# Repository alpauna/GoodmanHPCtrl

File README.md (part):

# GoodmanHPCtrl

ESP32-based controller for Goodman heatpumps with support for cooling, heating, and defrost modes.

> **⚠ Security note:** The device's web interface is plain HTTP only (no built-in TLS). For any access beyond a trusted local LAN, run it behind an HTTPS-terminating reverse proxy (Pangolin, Caddy, nginx, Cloudflare Tunnel, Tailscale Funnel, etc.) — never expose port 80 directly to an untrusted network. See [Network Access](#network-access).

## Web Interface

| Page | Screenshot |
|------|-----------|
| Home |  |
| Dashboard |  |
| Pins |  |
| Configuration |  |
| OTA Update |  |
| Log |  |
| Heap |  |

## Features

- **Relay control** — 4 output pins (FAN, Contactor, W-Heat, Reversing Valve) driven by 4 input signals (Low Pressure Switch, Defrost, Y-Cool, O-Heat)
- **Temperature monitoring** — Up to 6 OneWire (Dallas DS18B20) sensors (compressor, suction, ambient, condenser, liquid, vapor). OneWire sensors discovered on the bus are automatically merged with saved config on boot — new devices get default names and appear immediately without a config reset
- **Subcooling calculation** — Real-time subcooling diagnostic (CONDENSER_TEMP - LIQUID_TEMP) displayed on dashboard when both sensors are valid and compressor is running. Relevant for TXV systems to verify proper refrigerant charge
- **Ambient temp fallback** — 3-tier failover chain for ambient temperature: local OneWire sensor → weather data (MQTT subscription or OpenWeatherMap HTTP API, or both simultaneously) → ESP32 internal die temp. Actively fails up to the best available source every cycle. Configurable staleness timeout, test failover button, dashboard source indicator
- **Remote access** — REST API, WebSocket, MQTT (QoS 1), and CAN bus for monitoring and control
- **Dark/light theme** — Configurable dark/light theme with shared `theme.css` stylesheet. Persisted to SD card config, cached in localStorage for flash-free page loads. Instant preview on config page
- **Admin password protection** — HTTP Basic Auth on sensitive endpoints (`/config`, `/update`, `/ftp`). No password = open access
- **Password encryption** — All passwords (WiFi, MQTT, admin, FTP) encrypted at rest on SD card
- **Live dashboard** — Real-time dashboard at `/dashboard` with state banner, protection status pills with dynamic labels (LPS No Fault/Fault, Temp Ok/Low Temp, Comp Ok/OT, Suct LT Ok/LT, Suct Temp/High Suct with live temp reading, RV Pass/Fail with inline clear button), input/output grid, temperatures, and reboot button. Output indicators include inline status pills:
  -  **SC** (Short Cycle) — Shown on CNT output. Green when inactive, red when CNT short cycle protection delay is active (CNT was off < 5 min, waiting 30s before reactivation)
  -  **DFH** (Defrost Hold) — Shown on CNT, W, and RV outputs during the 3-phase defrost entry and exit transitions. On RV and W: red during entry Phase 1 or exit Phase 1 (pressure equalization). On CNT: red during entry Phase 2 or exit Phase 2 (waiting for CNT short cycle before compressor starts)
- **Pin table with manual override** — Auth-protected `/pins` page showing all GPIO inputs, outputs, and temperatures in a table. "Normal Mode Lockout" checkbox enables manual output control, bypassing the state machine for up to 30 minutes (auto-timeout). CNT enforces short cycle protection even in manual mode. Single auth prompt covers the entire lockout session. "Force Defrost" button triggers a software defrost cycle from HEAT mode (requires no active faults or manual override)
- **Temperature history** — Configurable CSV logging interval (30s-5min, default 2min) per sensor to SD card (`/temps/<sensor>/YYYY-MM-DD.csv`), rolling Canvas line charts on dashboard (6 sensors) with 1h/6h/24h/7d timeframe selector, auto-purge after 31 days
- **Web-based configuration** — HTML pages served from `/www/` on SD card for configuration, OTA updates, and monitoring
- **FTP server** — SimpleFTPServer with timed enable/disable (10/30/60 min) from config page. Configurable password (encrypted on SD card); defaults to `admin`/`admin` when not set. Defaults to OFF; auto-disables after timeout
- **OTA updates** — Firmware upload saves to SD card (`/firmware.new`), then apply to flash. Automatically backs up running firmware with build date metadata before flashing. Supports manual revert and automatic crash recovery (see [Crash Recovery](#crash-recovery))
- **SD card configuration** — WiFi, MQTT, and sensor settings stored as JSON on SD card
- **Multi-output logging** — Serial, MQTT, SD card with tar.gz compressed log rotation, and WebSocket streaming
- **In-memory log buffer** — 500-entry ring buffer in PSRAM, accessible via `/log` API endpoint
- **NTP time sync** — Automatic time synchronization from NTP servers, refreshes every 2 hours
- **I2C bus** — Initialized on GPIO8 (SDA) / GPIO9 (SCL) with automatic device scan at startup and `/i2c/scan` API endpoint
- **PSRAM support** — All heap allocations routed through PSRAM when available
- **WiFi AP fallback** — Configurable timeout (default 10 minutes) before switching to Access Point mode for OTA recovery and reconfiguration
- **CAN bus integration** — Optional CAN bus (ESP32 TWAI, 250 kbps) replaces physical Y/O thermostat wires with CAN messages from AThermostat. Publishes HP state, temperatures, and heartbeat. 10-second timeout safety shuts down compressor if CAN communication is lost. DFT/LPS safety inputs always remain physical. Configurable via `can.enabled` in config JSON. See `docs/canbus-goodmanhp-implementation.md`
- **Multi-unit support** — Configurable system name (max 20 chars, alphanumeric + spaces) and MQTT topic prefix. System name is used as the web UI brand, AP SSID, OLED display name, and auth realm. Multiple controllers can publish to the same MQTT broker with unique prefixes (e.g., `unit1/temps`, `unit2/temps`)
- **FreeRTOS compatible** — Uses `vTaskDelay()` instead of `delay()` for proper RTOS task yielding

## Architecture

### GoodmanHP Controller

The `GoodmanHP` class is the central controller that manages all I/O pins and the heat pump state machine:

- **Pin Management** — Maintains `std::map` collections for input and output pins
  - `addInput(name, pin)` / `addOutput(name, pin)` — Register pins
  - `getInput(name)` / `getOutput(name)` — Access individual pins
  - `getInputMap()` / `getOutputMap()` — Access full pin collections

- **Startup** — All outputs (FAN, CNT, W, RV) are turned OFF on controller startup

- **State Machine** — Tracks heat pump operating mode:
  - `OFF` — No active request
  - `HEAT` — Y input active (heating mode, RV off, W off)
  - `COOL` — Y and O inputs active (cooling mode, RV on, W off)
  - `DEFROST` — DFT emergency defrost or software defrost cycle (W on)
  - `ERROR` — Fault condition active (LPS low pressure); CNT shut down, W follows Y in HEAT mode (Y active, O not active), state updates blocked until fault clears
  - `LOW_TEMP` — Ambient temperature below threshold (default 20°F) for 10 continuous minutes; compressor off, auxiliary heat (W) on, auto-recovers when temp stays above threshold for 10 minutes

- **Output Control by State:**
  - **RV** (reversing valve): ON in COOL, OFF in HEAT/OFF
  - **W** (auxiliary heat): ON in DEFROST, ERROR (HEAT mode only), LOW_TEMP (HEAT mode only), and RV_FAIL (HEAT mode only); OFF otherwise. In COOL mode (Y+O), the system will not operate below 20°F
  - **CNT** (contactor): auto-activates when Y input becomes active, with short cycle protection: if CNT was off for less than 5 minutes, a 30-second delay is enforced before reactivation; if off for 5+ minutes, CNT activates immediately

- **Compressor Over-Temperature Protection** — When COMPRESSOR_TEMP reaches 240°F or above:
  - Immediately shuts down CNT to stop compressor
  - Keeps FAN running to cool the compressor
  - Blocks CNT activation while overtemp is active
  - Rechecks compressor temp every 1 minute
  - Auto-recovers when temp drops below 190°F (50°F hysteresis gap)
  - Logs fault condition and resolution time
  - Highest priority fault — checked before LPS and ambient temp

- **FAN Airflow Safety (Current Watchdog)** — Guarantees the outdoor fan is actually moving air whenever the compressor (CNT) is energized. See [BUG-013](docs/bugs/013-fan-no-current-while-compressor-running.md) for the field failure that motivated this protection:
  - **CNT ⇒ FAN invariant** — every code path that turns CNT ON also asserts FAN ON in the same block (state transitions, HEAT↔COOL cancel path, short-cycle re-activation, `updateState()` output validation) so the outputs cannot desynchronize
  - **Current-based liveness** — `FAN_CURRENT` (SCT-013-030 CT on ADS1115) is polled while CNT is on; if it stays below `FAN_MIN_RUNNING_AMPS` (default 0.3 A) for `FAN_NO_CURRENT_TIMEOUT_MS` (default 20 s), CNT is shut down and the controller latches `ERROR` state for `FAN_FAULT_ERROR_MS` (default 3 min)
  - **Debounced** — requires 3 consecutive low reads before arming the 20 s timer, filtering single-sample I2C glitches from bus contention with WiFi / AsyncTCP / SD log flush
  - **Auto-recovers** after the 3-minute lockout; the watchdog re-arms on the next CNT activation and re-latches if the fan still draws no current
  - Blocks CNT re-activation while the lockout is active; public accessors: `isFanFaultActive()`, `getFanFaultRemainingMs()`, `clearFanFault()`
  - Emits grep-friendly `FAN_FAULT:` and `FAN_SAFETY:` log tags with `Y=`, `O=`, `state=`, `amps=`, `pin=`, `elapsed=` for post-mortem log forensics
  - Depends on `CurrentSensor` producing trustworthy RMS: 60-sample window over ~4 line cycles, DC-mean subtraction, and all-zero I2C reads rejected as invalid rather than published as `0.00 A`

- **Suction Low-Temperature Protection** (COOL mode only) — Monitors SUCTION_TEMP for freezing conditions:
  - Warns when suction temp drops below 34°F
  - Shuts down CNT below 32°F (critically low), keeps FAN running
  - Blocks CNT activation while fault is active
  - Rechecks every 1 minute
  - Auto-recovers when temp rises above 40°F (8°F hysteresis from critical)
  - Auto-clears if mode changes away from COOL
  - Logs fault condition and resolution time

- **LPS Fault Protection** — When the LPS (Low Pressure Switch) input goes LOW:
  - Immediately shuts down CNT if running
  - Sets state to `ERROR`, blocking all state updates
  - Blocks CNT activation while fault is active
  - W (auxiliary heat) continuously follows Y during active fault: ON when Y active and O not active (HEAT mode), OFF when Y drops or O active (COOL mode). W is never turned on in COOL mode
  - Auto-recovers when LPS goes HIGH; W turned off, short-cycle protection (30s delay) is enforced on CNT reactivation
  - Publishes fault events via MQTT (`goodman/fault` topic)

- **Low Ambient Temperature Protection** — When AMBIENT_TEMP drops below the configurable threshold (default 20°F):
  - **10-minute validation delay** in both directions: temp must stay below threshold for 10 continuous minutes before entering LOW_TEMP, and above threshold for 10 continuous minutes before exiting. If temp reverses during the validation window, the pending transition is cancelled. Prevents fluttering near the threshold
  - Enters `LOW_TEMP` state: shuts down CNT, turns off FAN and RV
  - Turns on W (auxiliary heat) in HEAT mode only
  - If thermostat switches to COOL mode (Y+O) while in LOW_TEMP, W is turned off — no heating or cooling operates below 20°F in COOL mode
  - Blocks all compressor activation (CNT) while ambient temp is too low
  - Auto-recovers when temperature stays above threshold for 10 minutes
  - Threshold is configurable via `lowTemp.threshold` in SD card config

- **Ambient Temperature Fallback (3-Tier)** — When the local AMBIENT_TEMP OneWire sensor is unavailable, the system falls through a priority chain to maintain ambient awareness:
  1. **Local sensor** (primary) — OneWire DS18B20, highest accuracy
  2. **Weather data** (failover) — Cached outdoor temperature from a configurable source:
     - **MQTT**: Subscribes (QoS 1) to a configurable topic (e.g., `homeassistant/sensor/outdoor_temp/state`) and parses plain float payloads
     - **HTTP**: Polls OpenWeatherMap API at a configurable interval (default 10 min, range 1–60)
     - **MQTT + HTTP**: Both run simultaneously — MQTT delivers faster push updates while HTTP acts as a safety net if MQTT stops publishing. Most recent update from either source wins
  3. **ESP32 internal temp** (last resort) — Die temperature via `temperatureRead()`, converted C→F. Reads higher than true ambient but catches genuinely cold conditions
  - **Fail-up**: The fallback chain re-evaluates every 10s cycle and actively promotes to the best available source — INTERNAL→WEATHER when weather data arrives, any fallback→SENSOR when the real sensor recovers
  - Weather data is cached with a configurable staleness timeout (default 30 minutes). Stale weather with no local sensor falls through to ESP32 internal temp
  - `ambientSource` field in `/state` JSON and MQTT state tracks the active source: `"sensor"`, `"weather"`, or `"internal"`
  - Dashboard shows a source-aware ambient pill (green for sensor, orange for weather/internal) and a "Weather Amb (failover)" row with the cached temperature and age
  - Output state validator enforces CNT OFF when no ambient data is available (sensor invalid + no weather)
  - Config page "Weather Ambient Fallback" fieldset: source dropdown (None/MQTT/HTTP/MQTT + HTTP), conditional MQTT topic or HTTP API key/ZIP/country fields, staleness timeout
  - **Test Failover** button on config page forces the ambient sensor offline for 30 minutes to verify the fallback chain
  - Configured via `weather` section in SD card config JSON. API key encrypted with same `$AES$`/`$ENC$` scheme as other passwords

- **Input Pin Validation Delay** — All 4 input pins (LPS, DFT, Y, O) use a configurable debounce/validation delay (default 2 seconds) to prevent false triggers from electrical noise or transient signals:
  - Input pins are polled every 500ms via `onCheckInputQueue()` (direct GPIO polling, no ISR attachment required)
  - When a pin's live GPIO state differs from its confirmed state, a validation timer starts
  - After the delay expires, the GPIO is re-read to confirm the pin is still in the expected state
  - If the pin has reverted to its original state, the change is discarded as a false trigger and logged as a warning
  - `isActive()` returns the confirmed/debounced state, not the live GPIO — the state machine only sees validated inputs
  - `getPendingState()` prevents re-triggering while a validation is already in progress
  - Both activation (pin going HIGH) and deactivation (pin going LOW) go through the full delay
  - Configurable via `heatpump.inputDelay.ms` in config JSON (0–60 seconds, live — changes apply immediately to all input pins)

- **State Validation Delay** — After any state transition (e.g., OFF→HEAT, HEAT→COOL), the system holds the new state for a configurable period (default 30 seconds) before allowing another normal-priority state change. This prevents rapid state cycling:
  - **HIGH priority** states (OFF, ERROR) bypass the validation timer entirely
  - **NORMAL priority** states (HEAT, COOL, DEFROST, LOW_TEMP) are gated — blocked until the timer expires
  - LOW_TEMP has special handling: output protection (CNT/FAN/RV off, W management) is applied immediately, but the state label is deferred until validation completes
  - Dashboard shows a "State Hold" pill (blue) with countdown during validation
  - Configurable via `heatpump.stateValidation.delayMs` in config JSON (0–300 seconds, live)

- **Output State Validation** — Every 10 seconds, `validateOutputStates()` verifies all relay outputs match the expected state for the current operating mode using a table-driven approach:
  - **Global invariants** enforced first: W must never be on when O is active; CNT must be off during any blocking fault (priority: compressor overtemp > suction low temp > LPS fault > low temp > RV fail)
  - **Per-state table** defines expected output values: OFF=all off, COOL=RV on/W off, HEAT=RV off, DEFROST Ph3=RV+W on/FAN off, ERROR=CNT off, LOW_TEMP=CNT+FAN+RV off
  - **Transition phase rows** validated: COOL Trans Ph1/Ph2, HEAT Trans Ph1/Ph2, DEFROST Ph1/Ph2, Defrost Exit Ph1/Ph2
  - Mismatches are logged as errors and auto-corrected
  - Skipped during startup lockout and manual override only (transitions are now validated)
  - Manual override also bypasses the state validation timer so it doesn't interfere with manual pin control testing
  - Logs "State check OK" at info level every 30 seconds when all outputs are correct

- **Adaptive Defrost Bands** — Colder ambient temperatures cause faster ice buildup on the outdoor coil, requiring more frequent defrost cycles. Instead of a single fixed runtime threshold, the controller uses 3 ambient temperature bands — each with its own heat runtime threshold, minimum defrost duration, and condenser exit temperature:

  | Band | Ambient Range | Runtime Threshold | Min Defrost | Condenser Exit Temp |
  |------|--------------|-------------------|-------------|---------------------|
  | **Cold** | ≤ 23°F | 30 min | 2 min | 50°F |
  | **Mid** | 23–31°F | 60 min | 1.5 min | 55°F |
  | **Warm** | ≥ 31°F | 90 min | 1 min | 60°F |

  All values are configurable via the config page "Defrost Bands" fieldset. The two breakpoint temperatures (`coldMaxTemp`, `warmMinTemp`) define the band boundaries and can be adjusted independently.

  **How it works:**
  - The active band is selected every update cycle based on the current ambient temperature (using the same 3-tier fallback: sensor → weather → ESP32 internal temp)
  - When no ambient data is available, the system defaults to the **Warm** band (most conservative — longest runtime before defrost triggers)
  - When defrost starts, the active band's parameters are **snapshotted** and frozen for the duration of the cycle. If ambient temperature drifts mid-defrost (e.g., the sun comes up), the exit criteria stay stable — no mid-cycle parameter jumps
  - Dashboard and OLED display show the current band and progress: `Heat RT: 42m / 60m (Mid)`
  - `/state` JSON includes `defrostBand` (active band name) and `defrostBandThresholdMin` (active threshold in minutes)

  **Config JSON structure:**
  ```json
  "defrost": {
      "active": false,
      "coldMaxTemp": 23.0,
      "warmMinTemp": 31.0,
      "cold": { "runtimeThresholdMs": 1800000, "minRuntimeMs": 120000, "exitTempF": 50.0 },
      "mid":  { "runtimeThresholdMs": 3600000, "minRuntimeMs": 90000,  "exitTempF": 55.0 },
      "warm": { "runtimeThresholdMs": 5400000, "minRuntimeMs": 60000,  "exitTempF": 60.0 }
  }
  ```

  **Backward compatibility:** Devices upgrading from firmware with single-value defrost settings (`heatRuntimeThresholdMs`, `minRuntimeMs`, `exitTempF`) auto-migrate on first config load. The old values become the Warm band, and Mid/Cold bands are derived proportionally. Old keys are removed on the next config save.

- **Automatic Defrost (3-Phase Sequencing)** — After the active band's heat runtime threshold of accumulated CNT runtime in HEAT mode while DFT is active (coil temp ≤ 32°F, indicating icing conditions), initiates a 3-phase software defrost cycle for safe pressure equalization and output sequencing:

  **Phase 1 — Pressure Equalization** (`defrostTransition`):
  - All outputs OFF (CNT, FAN, W, RV)
  - Duration: `heatpump.shortCycle.rv` (default 30s)
  - Allows system pressures to equalize before reversing valve switches

  **Phase 2 — RV + W Engaged, CNT Hold** (`defrostCntPending`):
  - RV and W turned ON, CNT remains OFF
  - Duration: `heatpump.shortCycle.cnt` (default 30s)
  - Allows reversing valve to fully seat before compressor starts

  **Phase 3 — Active Defrost**:
  - CNT turned ON, defrost fully active
  - Runs for at least the active band's minimum defrost time before checking exit conditions
  - Rechecks CONDENSER_TEMP every 1 minute during defrost with logging
  - Exits when CONDENSER_TEMP >= the active band's exit temperature or 15-minute safety timeout

- **Defrost Exit Transition (3-Phase)** — When defrost completes (condenser temp reached or timeout), the system performs a reverse 3-phase sequence to safely switch the reversing valve back to heat position before restarting the compressor:

  **Exit Phase 1 — Pressure Equalization** (`defrostTransition` + `defrostExiting`):
  - CNT, FAN, and W turned OFF immediately; RV stays ON
  - Duration: `heatpump.shortCycle.rv` (default 30s)
  - Allows system pressures to equalize after compressor stops

  **Exit Phase 2 — RV Switch + CNT Hold** (`defrostCntPending` + `defrostExiting`):
  - RV turned OFF (switches back to heat position), CNT remains OFF
  - Duration: `heatpump.shortCycle.cnt` (default 30s)
  - Allows reversing valve to physically seat before compressor restarts

  **Exit Complete**:
  - CNT and FAN turned ON — system resumes normal HEAT mode operation
  - State machine has already transitioned from DEFROST to HEAT at exit start

  **Additional defrost behavior:**
  - Heat runtime only accumulates when DFT input is active (closed at 32°F, indicating icing conditions)
  - DFT turning off (temps > 32°F) clears accumulated runtime after a 30-second debounce — prevents false resets from intermittent DFT wire contact
  - Only COOL and DEFROST modes clear accumulated runtime; Y going off does not
  - Only HEAT mode adds time to accumulated runtime
  - Runtime persists to SD card every 5 minutes, restored on boot
  - **Y drop during defrost entry**: All outputs turn off (including W), transition flags are cleared, but `_softwareDefrost` stays set. When Y reactivates in HEAT mode, defrost restarts from Phase 1
  - **Y drop during defrost exit**: All outputs turn off, exit transition cancelled. Normal state machine resumes on Y reactivation
  - **COOL cancellation**: If the thermostat switches to COOL mode (O becomes active) during any phase of a pending defrost, the defrost is cancelled entirely, heat runtime is cleared, and the system enters normal COOL mode

- **HEAT→COOL Mode Transition (3-Phase)** — When switching from HEAT to COOL (O input activates), the reversing valve must switch safely with the compressor stopped:

  **Phase 1 — Pressure Equalization** (`coolTransition`):
  - CNT and FAN turned OFF, RV stays OFF (from HEAT position)
  - Duration: `heatpump.shortCycle.rv` (default 30s)

  **Phase 2 — RV On + CNT Hold** (`coolCntPending`):
  - RV turned ON (switches to COOL position), CNT remains OFF
  - Duration: `heatpump.shortCycle.cnt` (default 30s)

  **Complete**: CNT and FAN turned ON — normal COOL mode active. If RV is already ON (e.g., from defrost Phase 2/3→COOL), the transition is skipped.

- **COOL→HEAT Mode Transition (3-Phase)** — When switching from COOL to HEAT (O input deactivates), the reversing valve must switch safely with the compressor stopped:

  **Phase 1 — Pressure Equalization** (`heatTransition`):
  - CNT and FAN turned OFF, RV stays ON (from COOL position)
  - Duration: `heatpump.shortCycle.rv` (default 30s)

  **Phase 2 — RV Off + CNT Hold** (`heatCntPending`):
  - RV turned OFF (switches to HEAT position), CNT remains OFF
  - Duration: `heatpump.shortCycle.cnt` (default 30s)

  **Complete**: CNT and FAN turned ON — normal HEAT mode active.

  Both mode transitions abort on Y drop or state change (fault/LOW_TEMP), turning all outputs off.

### State Table

| State | Condition | FAN | CNT | RV | W | Notes |
|-------|-----------|-----|-----|----|---|-------|
| `OFF` | Y inactive | OFF | OFF | OFF | OFF | All outputs off |
| `HEAT` | Y active, O inactive | ON | ON | OFF | OFF | CNT has 30s short-cycle protection |
| `COOL` | Y active, O active | ON | ON | ON | OFF | Will not operate below 20°F |
| `DEFROST` Phase 1 | Pressure equalization (30s) | OFF | OFF | OFF | OFF | All outputs off for pressure equalization |
| `DEFROST` Phase 2 | RV + W engaged, CNT hold (30s) | OFF | OFF | ON | ON | Reversing valve seats before compressor starts |
| `DEFROST` Phase 3 | Active defrost | OFF | ON | ON | ON | Band-specific min time/exit temp (see Adaptive Defrost Bands), 15-min safety timeout |
| `HEAT` Exit Phase 1 | Defrost exit pressure equalization (30s) | OFF | OFF | ON | ON | RV+W stay on from defrost, CNT+FAN off |
| `HEAT` Exit Phase 2 | RV switch + CNT hold (30s) | OFF | OFF | OFF | OFF | RV switches back to heat position |
| `HEAT` Exit Complete | CNT+FAN resume | ON | ON | OFF | OFF | Normal HEAT mode resumes |
| `COOL` Trans Phase 1 | HEAT→COOL pressure equalization (30s) | OFF | OFF | OFF | OFF | CNT+FAN off before RV switches |
| `COOL` Trans Phase 2 | RV on, CNT hold (30s) | OFF | OFF | ON | OFF | RV seats before compressor starts |
| `HEAT` Trans Phase 1 | COOL→HEAT pressure equalization (30s) | OFF | OFF | ON | OFF | CNT+FAN off, RV still on from COOL |
| `HEAT` Trans Phase 2 | RV off, CNT hold (30s) | OFF | OFF | OFF | OFF | RV switches to HEAT position |
| `ERROR` | LPS fault (low pressure) | OFF | OFF | OFF | ON* | *W on only in HEAT mode (Y active, O inactive) |
| `LOW_TEMP` | Ambient < 20°F | OFF | OFF | OFF | ON* | *W on only in HEAT mode; W turns off if thermostat switches to COOL (Y+O) |
| `HEAT` + RV Fail | RV fail latched | ON | OFF | OFF | ON* | *W on only in HEAT mode; CNT blocked until cleared |

**Fault Conditions** (overlay on current state, block CNT activation):

| Fault | Condition | Trigger | Recovery | FAN | CNT | W | Priority |
|-------|-----------|---------|----------|-----|-----|---|----------|
| Compressor overtemp | COMPRESSOR_TEMP ≥ 240°F | Any mode | Temp < 190°F | ON | OFF | OFF | 1 (highest) |
| Suction low temp | SUCTION_TEMP < 32°F | COOL mode only | Temp > 40°F | ON | OFF | OFF | 2 |
| LPS fault | LPS input LOW | Any mode | LPS goes HIGH | OFF | OFF | ON* | 3 |
| Low ambient temp | AMBIENT_TEMP < 20°F for 10 min | Any mode | Temp ≥ 20°F for 10 min | OFF | OFF | ON* | 4 |
| RV fail | SUCTION_TEMP ≥ 140°F during defrost | Defrost only | Manual clear via dashboard/config | ON | OFF | ON* | Latched |

\* W on only in HEAT mode (Y active, O inactive); never activated in COOL mode (Y+O).

**Fault Priority:** Compressor overtemp > Suction low temp > LPS fault > Low ambient temp. Higher-priority faults take precedence; lower-priority checks are skipped while a higher-priority fault is active.

### Class Structure

| Class | Purpose |
|-------|---------|
| `GoodmanHP` | Central controller with pin maps, temp sensors, and state machine |
| `InputPin` | Digital/analog input with polling-based validation delay, confirmed-state debouncing, callbacks |
| `OutPin` | Output relay with delay, PWM support, state tracking, hardware state validation |
| `TempSensor` | OneWire (DS18B20) temperature sensor with callbacks. 6 default names: COMPRESSOR, SUCTION, AMBIENT, CONDENSER, LIQUID, VAPOR |
| `Config` | SD card and JSON configuration management |
| `Logger` | Multi-output logging with tar.gz rotation, ring buffer, and WebSocket streaming |
| `WebHandler` | AsyncWebServer (port 80) with REST API and WebSocket |
| `MQTTHandler` | MQTT client with auto-reconnect and topic publishing |

## Hardware

**Supported boards:**
- Freenove ESP32-S3-WROOM (primary)
- ESP32 DevKit

**GPIO Pin Mapping (ESP32-S3):**

| Pin | GPIO | Direction | Description |
|-----|------|-----------|-------------|
| LPS | 15 | Input | Low Pressure Switch |
| DFT | 16 | Input | Defrost signal |
| Y | 17 | Input | Compressor request (heat or cool) |
| O | 18 | Input | Reversing valve signal (cool mode) |
| FAN | 4 | Output | Fan relay |
| CNT | 5 | Output | Contactor relay (3s delay) |
| W | 6 | Output | Heating relay |
| RV | 7 | Output | Reversing valve relay |
| SDA | 8 | I/O | I2C data |
| SCL | 9 | I/O | I2C clock |
| OneWire | 21 | I/O | Temperature sensor bus |
| CAN TX | 38 | Output | CAN bus transmit (TWAI) |
| CAN RX | 14 | Input | CAN bus receive (TWAI) |

**I2C Devices:**

| Device | Address | Description |
|--------|---------|-------------|
| SSD1306 | 0x3C | 128x64 OLED display (5-page auto-cycling status) |
| ADS1115 | 0x48 | 16-bit ADC for CT clamp current sensing |

### 3D Printed Shell

The enclosure is an EasyEDA-exported 3D shell, post-processed with FreeCAD Python scripts for thicker walls, a flipped mating profile, and mounting hardware. All files are in the `shell/` directory.

**Shell files:**

| File | Description |
|------|-------------|
| `3DShell_GoodmanHPv3_T_3mm_TC.step/.stl` | Original top shell (3mm walls, tongue on outer half, TC mount) |
| `3DShell_GoodmanHPv3_B_3mm.step/.stl` | Original bottom shell (3mm walls, groove on outer half) |
| `3DShell_GoodmanHPv3_T_3.5mm_TC_flipped.step/.stl` | Modified top shell (3.5mm walls, groove replaces tongue) |
| `3DShell_GoodmanHPv3_B_3.5mm_flipped.step/.stl` | Modified bottom shell (3.5mm walls, tongue replaces groove) |
| `modify_top.py` | FreeCAD script to generate the modified top shell |
| `modify_bottom.py` | FreeCAD script to generate the modified bottom shell |
| `cutout.py` | Reusable FreeCAD utility library for cutout, standoff, and mounting operations |

**Why the mating profile was flipped:** The original design had a tongue (raised band) on the top shell mating rim. When 3D printed, this thin horizontal band is prone to layer separation because it prints as an unsupported overhang at the shell's open edge. Moving the tongue to the bottom shell and the groove to the top eliminates this — the bottom tongue prints vertically up from the floor (strong layer adhesion), and the top groove is simply a recess in a solid wall.

**Modifications applied:**

1. **Wall thickening (3mm to 3.5mm)** — 0.5mm added to the outer face of all 4 walls. Inner cavity dimensions unchanged so the PCB still fits. Wall cutouts (connector openings on right and back walls) are preserved by pre-cutting matching holes in the thickening ring before fusing.

2. **Mating profile flip** — The rabbet/step joint between shells was inverted:
   - **Bottom**: Original groove (Z=31-35) filled, new outer tongue added with 0.10mm clearance per side
   - **Top**: Original tongue (Z=28-32) removed, new inner lip + outer groove cut

3. **M3 screw pillar** — 5mm OD, 3mm tall pillar on the top shell ceiling for mounting the MAX6675 thermocouple board, with M3 (2.5mm) through-hole centered in the pillar

**Utility library (`cutout.py`):**

Composable functions for shell modifications. Each takes a `Part.Shape` and returns a modified shape. OCCT boolean operation quirks (oversized plugs, Z range matching, flush trimming) are handled internally:

| Function | Purpose |
|----------|---------|
| `rectangular_cutout()` | Cut a window through a Z-normal surface |
| `reposition_cutout()` | Plug an existing cutout and re-cut at a new position (3-step: oversized plug, matching-Z cut, flush trim) |
| `add_standoff()` | Fuse a cylindrical pillar onto a surface (with auto-trim for reliable OCCT fuse) |
| `drill_hole()` | Vertical through-hole along Z axis |
| `drill_hole_lateral()` | Horizontal through-hole along X or Y axis (screw holes through walls) |
| `add_standoffs_with_holes()` | Multiple standoffs + centered screw holes (convenience combo) |
| `wall_ring()` | Rectangular ring (outer box minus inner box) for wall thickening and mating profiles |
| `z_probe()` | Probe Z intersections at an XY point (verification) |
| `verify_cutout()` | Check a rectangular cutout is fully open (probes center + corners) |
| `verify_solid()` | Check material exists at a point between two Z levels |

Example usage:
```python
from cutout import reposition_cutout, add_standoff, drill_hole

# Reposition an LCD cutout (plug old hole, cut new, trim flush — all in one call)
result = reposition_cutout(result,
    old_x1=-38.48, old_y1=59.59, old_x2=-11.43, old_y2=76.59,
    new_x1=-38.48, new_y1=61.59, new_x2=-11.43, new_y2=77.59,
    z_inner=48.50, z_outer=51.50)

# Add a mounting standoff below the ceiling
result = add_standoff(result, cx=-63.76, cy=67.14,
    z_surface=48.50, height=3.0, radius=2.5, z_outer=51.50)

# Drill a screw hole through the standoff
result = drill_hole(result, cx=-63.76, cy=67.14,
    z_bottom=45.50, z_top=51.50, radius=1.25)
```

**Regenerating modified shells:**

```bash
# Requires FreeCAD installed (sudo apt install freecad)
freecadcmd shell/modify_top.py
freecadcmd shell/modify_bottom.py
```

**Key geometry constants (all in mm, origin at EasyEDA export origin):**

| Constant | Value | Description |
|----------|-------|-------------|
| Outer walls | X[-98.26, 4.92] Y[-32.48, 97.12] | Original 3mm outer face |
| Inner walls | X[-95.26, 1.92] Y[-29.48, 94.12] | Original 3mm inner face |
| New outer | X[-98.76, 5.42] Y[-32.98, 97.62] | After 0.5mm thickening |
| Bottom mating zone | Z=31 to Z=35 | Groove (original) / Tongue (modified) |
| Top mating zone | Z=28 to Z=32 | Tongue (original) / Groove (modified) |
| Right wall cutout | Y[47, 88.5] Z[7, 24] | Connector opening, +X wall |
| Back wall lower cutout | X[-50, -35] Z[6, 13] | Opening, +Y wall |
| Back wall upper cutout | X[-89.5, -3.5] Z[14, 17] | Opening, +Y wall |

### Modifying EasyEDA 3D Shell Exports with Claude Code

EasyEDA exports PCB enclosures as STEP files with thin walls (typically 1.5mm). These often need post-processing — thicker walls, mating features, mounting hardware, cutouts — which can be done programmatically via FreeCAD's Python API and Claude Code. Below is a reusable prompt template and the key lessons learned from this project's shell modifications.

**Prerequisites:** `freecad` package installed (`sudo apt install freecad`), STEP files exported from EasyEDA's 3D shell generator.

**Prompt template** — adapt the bracketed sections to your project:

> I have EasyEDA-exported STEP enclosure shells at `[path/to/shells/]`:
> - `[Bottom_Shell.step]` — bottom half, open top
> - `[Top_Shell.step]` — top half, open bottom
>
> The shells have [1.5mm] walls. I need the following modifications:
>
> 1. **Wall thickening** — Increase wall thickness from [1.5mm] to [3mm] by expanding outward. Keep inner cavity dimensions identical to the original so the PCB still fits. Preserve all interior features (screw pillars, standoffs, alignment posts) from the original STEP by extracting them via boolean intersection and fusing them back into the thickened shell.
>
> 2. **Mating joint** — Add a rabbet/step joint between top and bottom shells in the overlap zone where both rims meet:
>    - Bottom: remove outer half of wall for [4mm] from the rim (groove)
>    - Top: remove inner half of wall in the overlap zone + add outer-half tongue extending [4mm] below the rim with [0.2mm] clearance
>    - The tongue must overlap at least [2mm] into existing wall geometry above the rim for OCCT fuse to succeed (coincident-face workaround)
>
> 3. **Screw holes** — Drill [M1.2] through-holes at [left and right wall midpoints], centered in the interlocking overlap zone so the screw passes through both the tongue and groove lip
>
> 4. **Cutouts** — Cut rectangular openings in the top shell for: [LCD window at X1,Y1 to X2,Y2], [wire pass-through at ...], [connector at ...]
>
> 5. **Mounting features** — Add a screw pillar on the inner ceiling of the top shell at [position] for mounting a [component]. [Xmm] OD, [Xmm] tall, [MX] tap hole
>
> Write a FreeCAD Python script (`freecadcmd script.py`) that loads the STEP files, performs all modifications via boolean operations, and exports both STL and STEP. Include a verification section that cross-sections the results and prints geometry at key Z levels.

**Key lessons for FreeCAD/OCCT boolean operations:**

| Issue | Symptom | Fix |
|-------|---------|-----|
| Coincident face fuse failure | `fuse()` adds volume but geometry doesn't extend beyond shared face | Extend the new body 1-2mm past the shared face into existing solid so they overlap, not just touch |
| `makeOffsetShape` fails on complex shells | Exception or degenerate result | Rebuild parametrically: create outer box, cut inner cavity, extract+fuse interior features from original via `common()` |
| Thickening shifts features | Mounting tabs, screw pillars stay at original positions | After thickening, extract features by region (`common()` with probe box), `translated()` to correct position, cut old + fuse shifted |
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
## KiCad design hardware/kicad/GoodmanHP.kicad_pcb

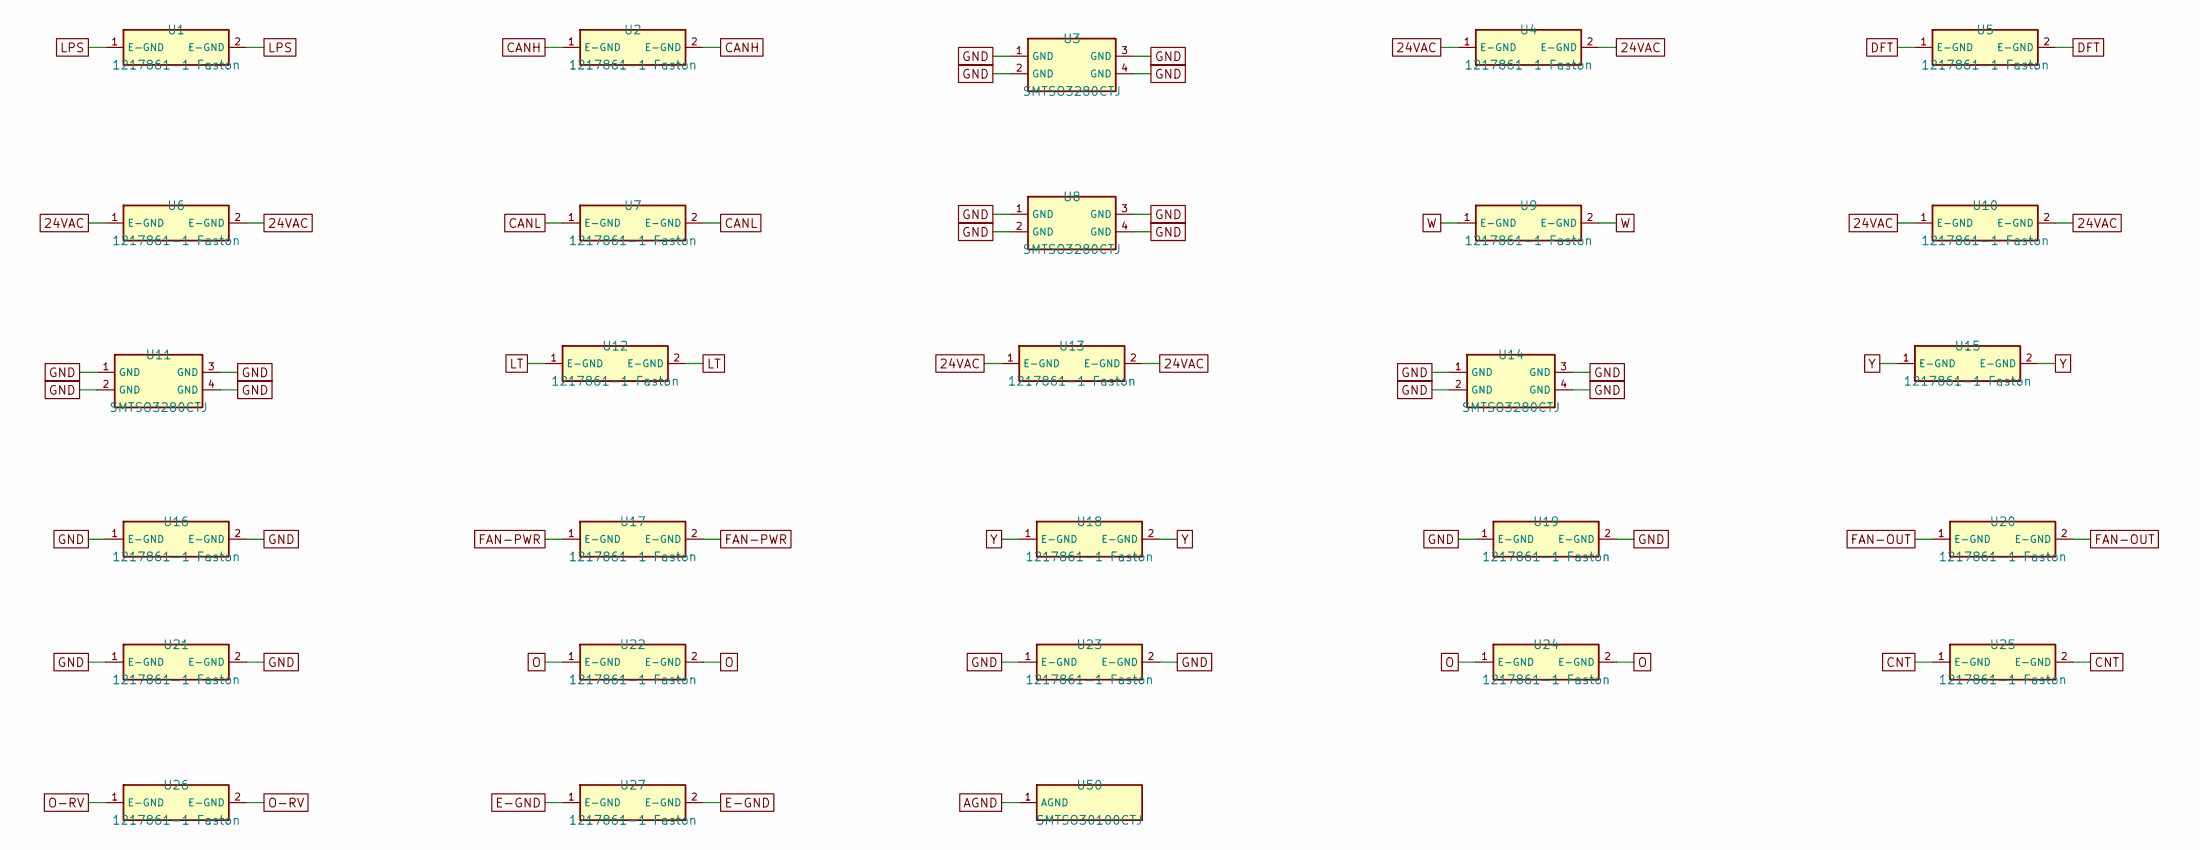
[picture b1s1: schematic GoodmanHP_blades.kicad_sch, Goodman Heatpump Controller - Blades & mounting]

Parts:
U1, U2, U4, U5, U6, U7, U9, U10, U12, U13, U15, U16, U17, U18, U19, U20, U21, U22, U23, U24, U25, U26, U27: 1217861-1 Faston; 1217861-1; LCSC C428480
U3, U8, U11, U14: SMTSO3280CTJ; SMD_BD5.6-L5.6-W5.6-D4.1; LCSC C2928174
U50: SMTSO30100CTJ; SCREW-SMD_BD5.6-D4.1-H10; LCSC C2916370

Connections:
24VAC: U4.1, U4.2, U6.1, U6.2, U10.1, U10.2, U13.1, U13.2; also elsewhere on the board
AGND: U50.1; also elsewhere on the board
CANH: U2.1, U2.2; also elsewhere on the board
CANL: U7.1, U7.2; also elsewhere on the board
CNT: U25.1, U25.2; also elsewhere on the board
DFT: U5.1, U5.2; also elsewhere on the board
E-GND: U27.1, U27.2; also elsewhere on the board
FAN-OUT: U20.1, U20.2; also elsewhere on the board
FAN-PWR: U17.1, U17.2; also elsewhere on the board
GND: U3.1, U3.2, U3.3, U3.4, U8.1, U8.2, U8.3, U8.4, U11.1, U11.2, U11.3, U11.4, U14.1, U14.2, U14.3, U14.4, U16.1, U16.2, U19.1, U19.2, U21.1, U21.2, U23.1, U23.2; also elsewhere on the board
LPS: U1.1, U1.2; also elsewhere on the board
LT: U12.1, U12.2; also elsewhere on the board
O: U22.1, U22.2, U24.1, U24.2; also elsewhere on the board
O-RV: U26.1, U26.2; also elsewhere on the board
W: U9.1, U9.2; also elsewhere on the board
Y: U15.1, U15.2, U18.1, U18.2; also elsewhere on the board

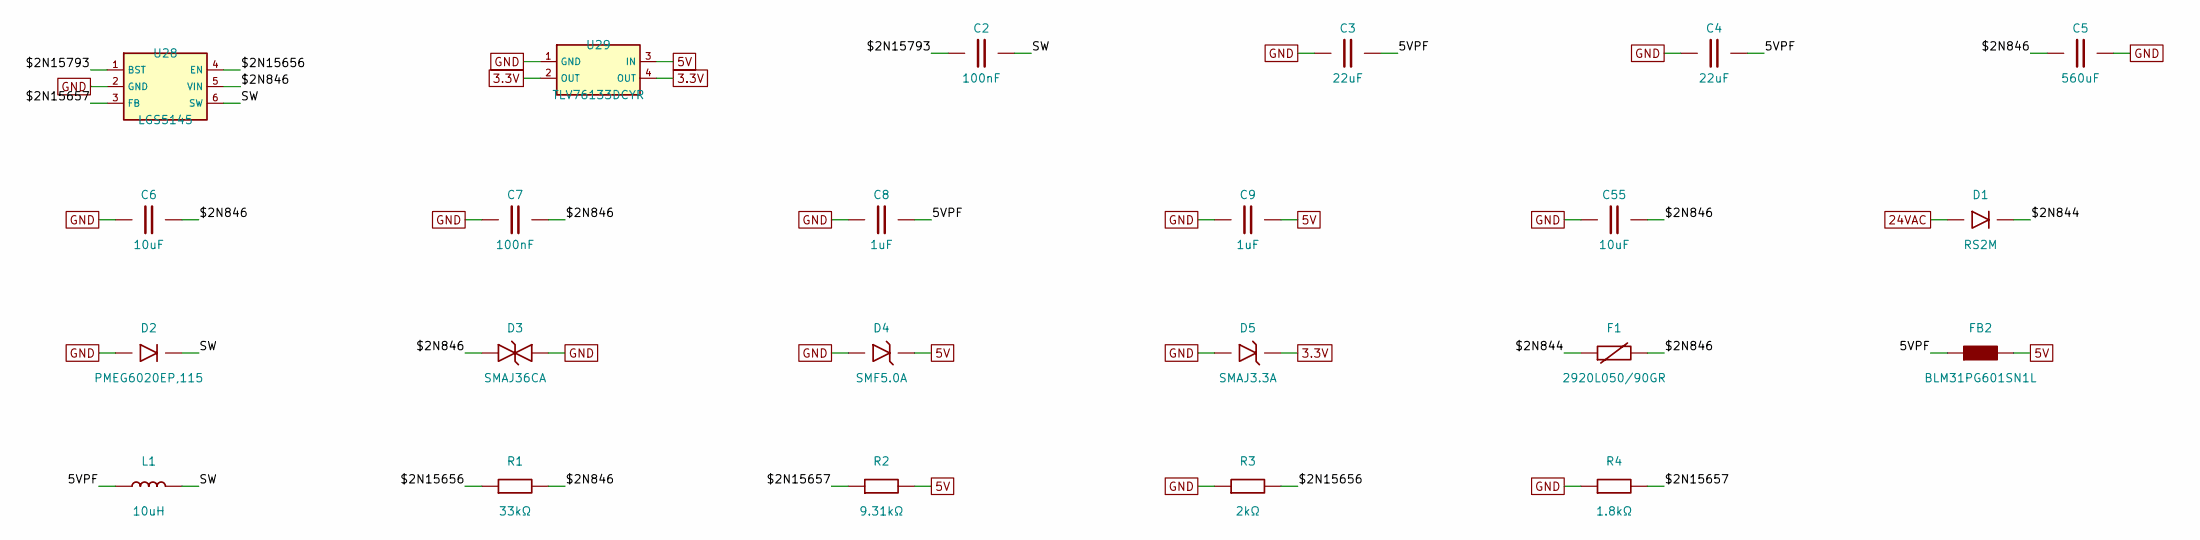
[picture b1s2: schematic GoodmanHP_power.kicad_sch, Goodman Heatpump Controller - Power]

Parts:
C2, C7: 100nF; C0402; LCSC C77020
C3, C4: 22uF; C0805; LCSC C907991
C5: 560uF; CAP-TH_BD10.0-P5.00-D1.0-FD_1; LCSC C49309240
C6, C55: 10uF; C1210; LCSC C437568
C8, C9: 1uF; C0201; LCSC C76929
D1: RS2M; SMA_L4.3-W2.7-LS5.1-RD; LCSC C908426
D2: PMEG6020EP,115; SOD-128_L3.7-W2.5-LS4.7-FD; LCSC C179433
D3: SMAJ36CA; SMA_L4.2-W2.7-LS5.0-BI; LCSC C908830
D4: SMF5.0A; SOD-123FL_L2.8-W1.9-LS3.7-RD; LCSC C2857263
D5: SMAJ3.3A; SMA_L4.3-W2.7-LS5.1-RD; LCSC C22365220
F1: 2920L050/90GR; F2920; LCSC C41414044
FB2: BLM31PG601SN1L; L1206; LCSC C16902
L1: 10uH; IND-SMD_L2.5-W2.0; LCSC C5832376
R1: 33kΩ; R0201; LCSC C473534
R2: 9.31kΩ; R0201; LCSC C423401
R3: 2kΩ; R0201; LCSC C851709
R4: 1.8kΩ; R0201; LCSC C473568
U28: LGS5145; SOT-23-6_L2.9-W1.7-P0.95-LS2.8-BL; LCSC C5123971
U29: TLV76133DCYR; SOT-223-4_L6.5-W3.5-P2.30-LS7.0-TR; LCSC C7527500

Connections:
3.3V: D5.1 (K), U29.2 (OUT), U29.4 (OUT); also elsewhere on the board
5V: C9.2, D4.1 (K), FB2.2, R2.2, U29.3 (IN); also elsewhere on the board
5VPF: C3.2, C4.2, C8.2, FB2.1, L1.1
24VAC: D1.2 (A); also elsewhere on the board
$2N844: D1.1 (K), F1.1
$2N846: C5.1, C6.2, C7.2, C55.2, D3.1, F1.2, R1.2, U28.5 (VIN)
$2N15656: R1.1, R3.2, U28.4 (EN)
$2N15657: R2.1, R4.2, U28.3 (FB)
$2N15793: C2.1, U28.1 (BST)
GND: C3.1, C4.1, C5.2, C6.1, C7.1, C8.1, C9.1, C55.1, D2.2 (A), D3.2, D4.2 (A), D5.2 (A), R3.1, R4.1, U28.2 (GND), U29.1 (GND); also elsewhere on the board
SW: C2.2, D2.1 (K), L1.2, U28.6 (SW)

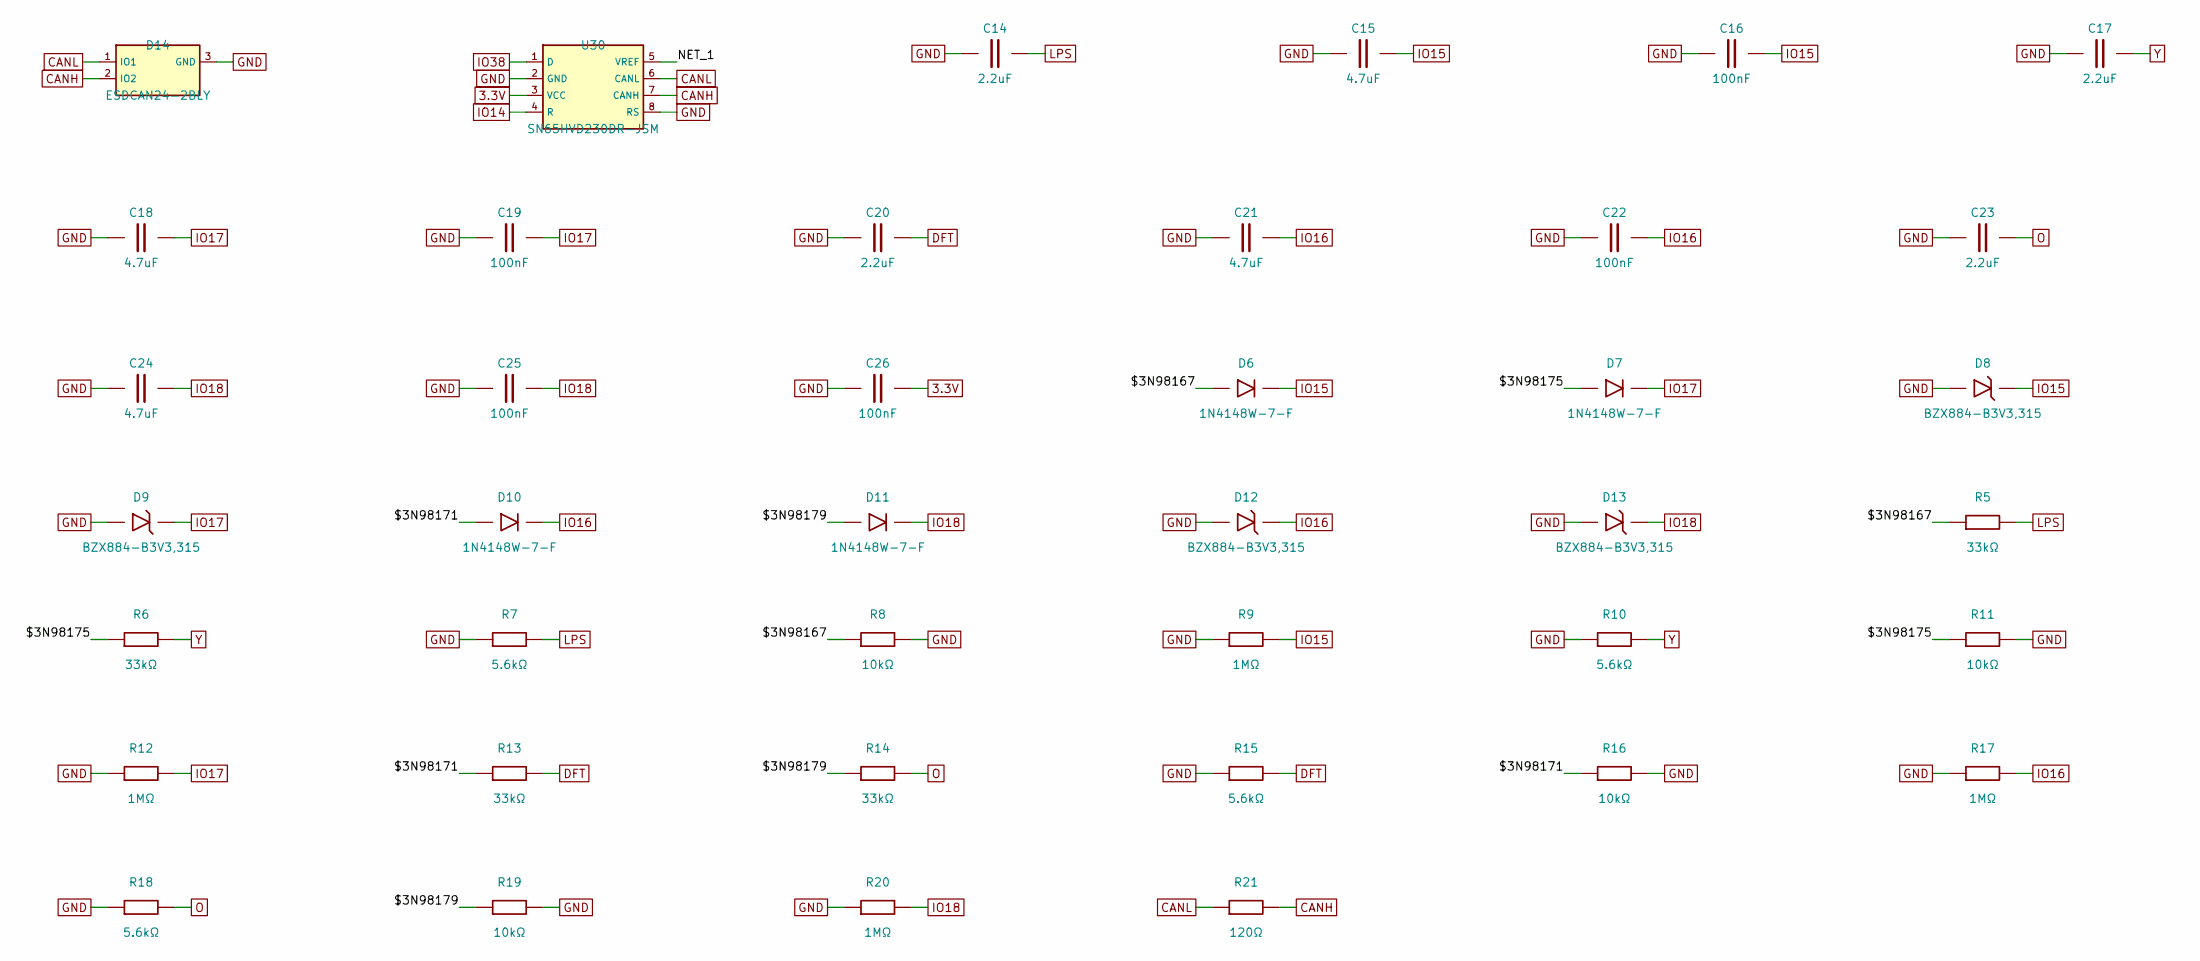
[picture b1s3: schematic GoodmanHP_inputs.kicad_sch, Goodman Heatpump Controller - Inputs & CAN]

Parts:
C14, C17, C20, C23: 2.2uF; C0805; LCSC C22367838
C15, C18, C21, C24: 4.7uF; C0402; LCSC C20624278
C16, C19, C22, C25, C26: 100nF; C0201; LCSC C85923
D6, D7, D10, D11: 1N4148W-7-F; SOD-123_L2.7-W1.6-LS3.7-RD-1; LCSC C83528
D8, D9, D12, D13: BZX884-B3V3,315; SOD-882_L1.0-W0.6-RD; LCSC C551199
D14: ESDCAN24-2BLY; SOT-23-3_L2.9-W1.3-P1.90-LS2.4-BL-2; LCSC C2937021
R5, R6, R13, R14: 33kΩ; R0201; LCSC C473534
R7, R10, R15, R18: 5.6kΩ; R0805; LCSC C441985
R8, R11, R16, R19: 10kΩ; R0201; LCSC C473048
R9, R12, R17, R20: 1MΩ; R0201; LCSC C295786
R21: 120Ω; R0805; LCSC C844392
U30: SN65HVD230DR-JSM; SOP-8_L4.9-W3.9-P1.27-LS6.0-BL; LCSC C46596299

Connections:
3.3V: C26.2, U30.3 (VCC); also elsewhere on the board
$3N98167: D6.2 (A), R5.1, R8.1
$3N98171: D10.2 (A), R13.1, R16.1
$3N98175: D7.2 (A), R6.1, R11.1
$3N98179: D11.2 (A), R14.1, R19.1
CANH: D14.2 (IO2), R21.2, U30.7 (CANH); also elsewhere on the board
CANL: D14.1 (IO1), R21.1, U30.6 (CANL); also elsewhere on the board
DFT: C20.2, R13.2, R15.2; also elsewhere on the board
GND: C14.1, C15.1, C16.1, C17.1, C18.1, C19.1, C20.1, C21.1, C22.1, C23.1, C24.1, C25.1, C26.1, D8.2 (A), D9.2 (A), D12.2 (A), D13.2 (A), D14.3 (GND), R7.1, R8.2, R9.1, R10.1, R11.2, R12.1, R15.1, R16.2, R17.1, R18.1, R19.2, R20.1, U30.2 (GND), U30.8 (RS); also elsewhere on the board
IO14: U30.4 (R); also elsewhere on the board
IO15: C15.2, C16.2, D6.1 (K), D8.1 (K), R9.2; also elsewhere on the board
IO16: C21.2, C22.2, D10.1 (K), D12.1 (K), R17.2; also elsewhere on the board
IO17: C18.2, C19.2, D7.1 (K), D9.1 (K), R12.2; also elsewhere on the board
IO18: C24.2, C25.2, D11.1 (K), D13.1 (K), R20.2; also elsewhere on the board
IO38: U30.1 (D); also elsewhere on the board
LPS: C14.2, R5.2, R7.2; also elsewhere on the board
NET_1: U30.5 (VREF)
O: C23.2, R14.2, R18.2; also elsewhere on the board
Y: C17.2, R6.2, R10.2; also elsewhere on the board

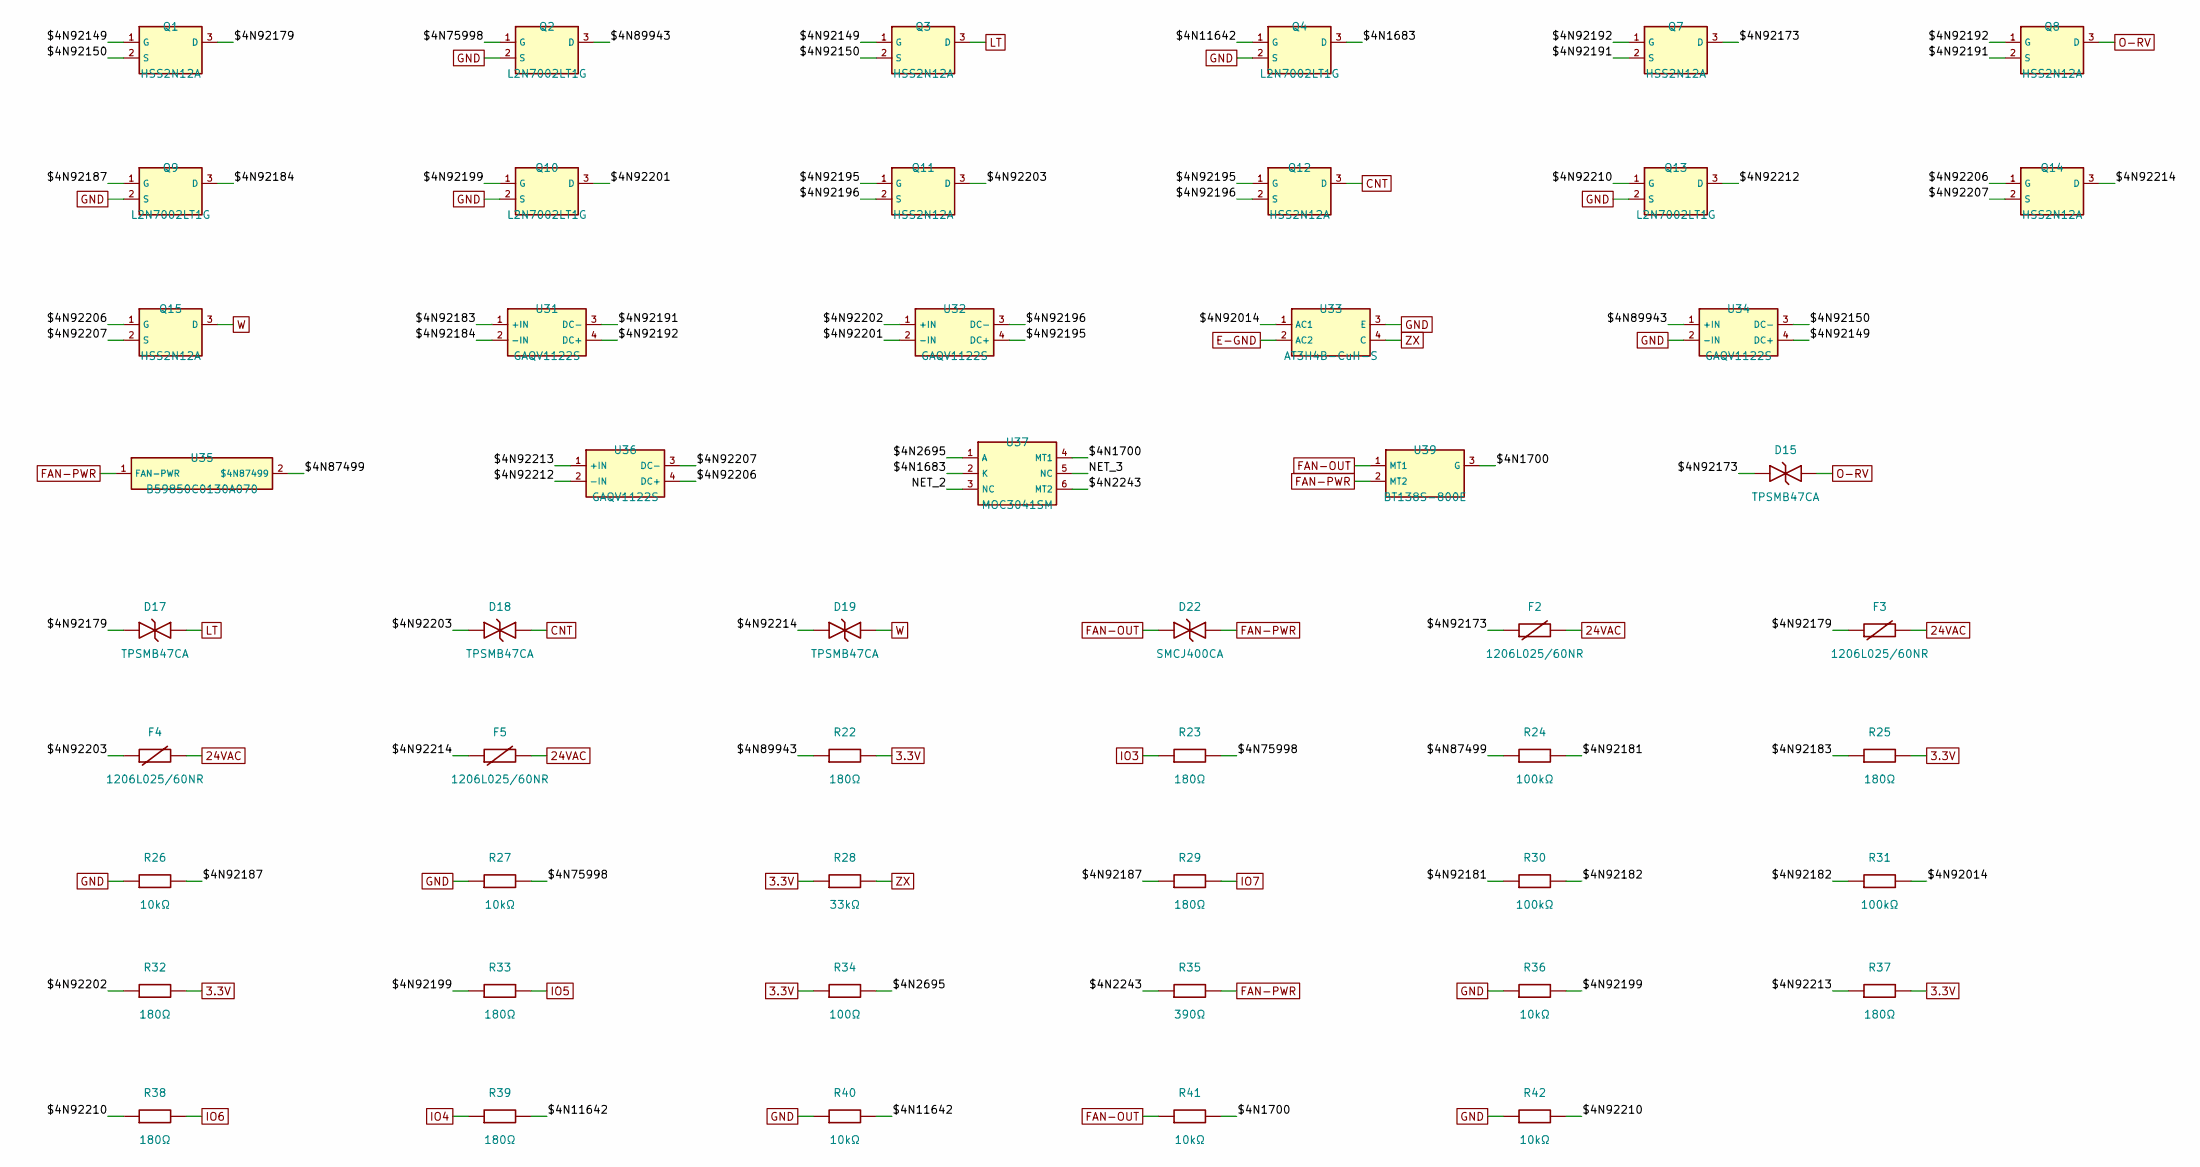
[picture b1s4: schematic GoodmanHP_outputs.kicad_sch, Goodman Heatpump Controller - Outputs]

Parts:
D15, D17, D18, D19: TPSMB47CA; SMB_L4.3-W3.6-LS5.4-BI; LCSC C1975322
D22: SMCJ400CA; SMCG_L6.8-W5.8-LS7.9-BI; LCSC C5294118
F2, F3, F4, F5: 1206L025/60NR; F1206; LCSC C47345582
Q1, Q3, Q7, Q8, Q11, Q12, Q14, Q15: HSS2N12A; SOT-23-3_L3.0-W1.7-P0.95-LS2.9-BR; LCSC C53243986
Q2, Q4, Q9, Q10, Q13: L2N7002LT1G; SOT-23_L2.9-W1.3-P1.90-LS2.4-BR; LCSC C12779
R22, R23, R25, R29, R32, R33, R37, R38, R39: 180Ω; R0201; LCSC C965335
R24, R30, R31: 100kΩ; R0805_NEW; LCSC C96346
R26, R27, R36, R40, R42: 10kΩ; R0201; LCSC C473048
R28: 33kΩ; R0201; LCSC C473534
R34: 100Ω; R0201; LCSC C77623
R35: 390Ω; R1210; LCSC C2960731
R41: 10kΩ; R0603; LCSC C2906982
U31, U32, U34, U36: GAQV1122S; SOP-4_L4.3-W4.4-P2.54-LS6.8-TR; LCSC C22385006
U33: AT3H4B-CuH-S; SSOP-4_L2.7-W4.6-P1.27-LS7.0-TL; LCSC C20612635
U35: B59850C0130A070; RES-TH_L11.0-W5.0-P5.00-D0.8; LCSC C125471
U37: MOC3041SM; SMD-6_L8.8-W6.4-P2.54-LS9.4-BL; LCSC C22373366
U39: BT138S-800E; TO-252-2_L6.6-W6.1-P4.57-LS10.1-BR-CW; LCSC C5380690

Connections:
3.3V: R22.2, R25.2, R28.1, R32.2, R34.1, R37.2; also elsewhere on the board
24VAC: F2.2, F3.2, F4.2, F5.2; also elsewhere on the board
$4N1683: Q4.3 (D), U37.2 (K)
$4N1700: R41.2, U37.4 (MT1), U39.3 (G)
$4N2243: R35.1, U37.6 (MT2)
$4N2695: R34.2, U37.1 (A)
$4N11642: Q4.1 (G), R39.2, R40.2
$4N75998: Q2.1 (G), R23.2, R27.2
$4N87499: R24.1, U35.2 ($4N87499)
$4N89943: Q2.3 (D), R22.1, U34.1 (+IN)
$4N92014: R31.2, U33.1 (AC1)
$4N92149: Q1.1 (G), Q3.1 (G), U34.4 (DC+)
$4N92150: Q1.2 (S), Q3.2 (S), U34.3 (DC-)
$4N92173: D15.1, F2.1, Q7.3 (D)
$4N92179: D17.1, F3.1, Q1.3 (D)
$4N92181: R24.2, R30.1
$4N92182: R30.2, R31.1
$4N92183: R25.1, U31.1 (+IN)
$4N92184: Q9.3 (D), U31.2 (-IN)
$4N92187: Q9.1 (G), R26.2, R29.1
$4N92191: Q7.2 (S), Q8.2 (S), U31.3 (DC-)
$4N92192: Q7.1 (G), Q8.1 (G), U31.4 (DC+)
$4N92195: Q11.1 (G), Q12.1 (G), U32.4 (DC+)
$4N92196: Q11.2 (S), Q12.2 (S), U32.3 (DC-)
$4N92199: Q10.1 (G), R33.1, R36.2
$4N92201: Q10.3 (D), U32.2 (-IN)
$4N92202: R32.1, U32.1 (+IN)
$4N92203: D18.1, F4.1, Q11.3 (D)
$4N92206: Q14.1 (G), Q15.1 (G), U36.4 (DC+)
$4N92207: Q14.2 (S), Q15.2 (S), U36.3 (DC-)
$4N92210: Q13.1 (G), R38.1, R42.2
$4N92212: Q13.3 (D), U36.2 (-IN)
$4N92213: R37.1, U36.1 (+IN)
$4N92214: D19.1, F5.1, Q14.3 (D)
CNT: D18.2, Q12.3 (D); also elsewhere on the board
E-GND: U33.2 (AC2); also elsewhere on the board
FAN-OUT: D22.1, R41.1, U39.1 (MT1); also elsewhere on the board
FAN-PWR: D22.2, R35.2, U35.1 (FAN-PWR), U39.2 (MT2); also elsewhere on the board
GND: Q2.2 (S), Q4.2 (S), Q9.2 (S), Q10.2 (S), Q13.2 (S), R26.1, R27.1, R36.1, R40.1, R42.1, U33.3 (E), U34.2 (-IN); also elsewhere on the board
IO3: R23.1; also elsewhere on the board
IO4: R39.1; also elsewhere on the board
IO5: R33.2; also elsewhere on the board
IO6: R38.2; also elsewhere on the board
IO7: R29.2; also elsewhere on the board
LT: D17.2, Q3.3 (D); also elsewhere on the board
NET_2: U37.3 (NC)
NET_3: U37.5 (NC)
O-RV: D15.2, Q8.3 (D); also elsewhere on the board
W: D19.2, Q15.3 (D); also elsewhere on the board
ZX: R28.2, U33.4 (C); also elsewhere on the board
